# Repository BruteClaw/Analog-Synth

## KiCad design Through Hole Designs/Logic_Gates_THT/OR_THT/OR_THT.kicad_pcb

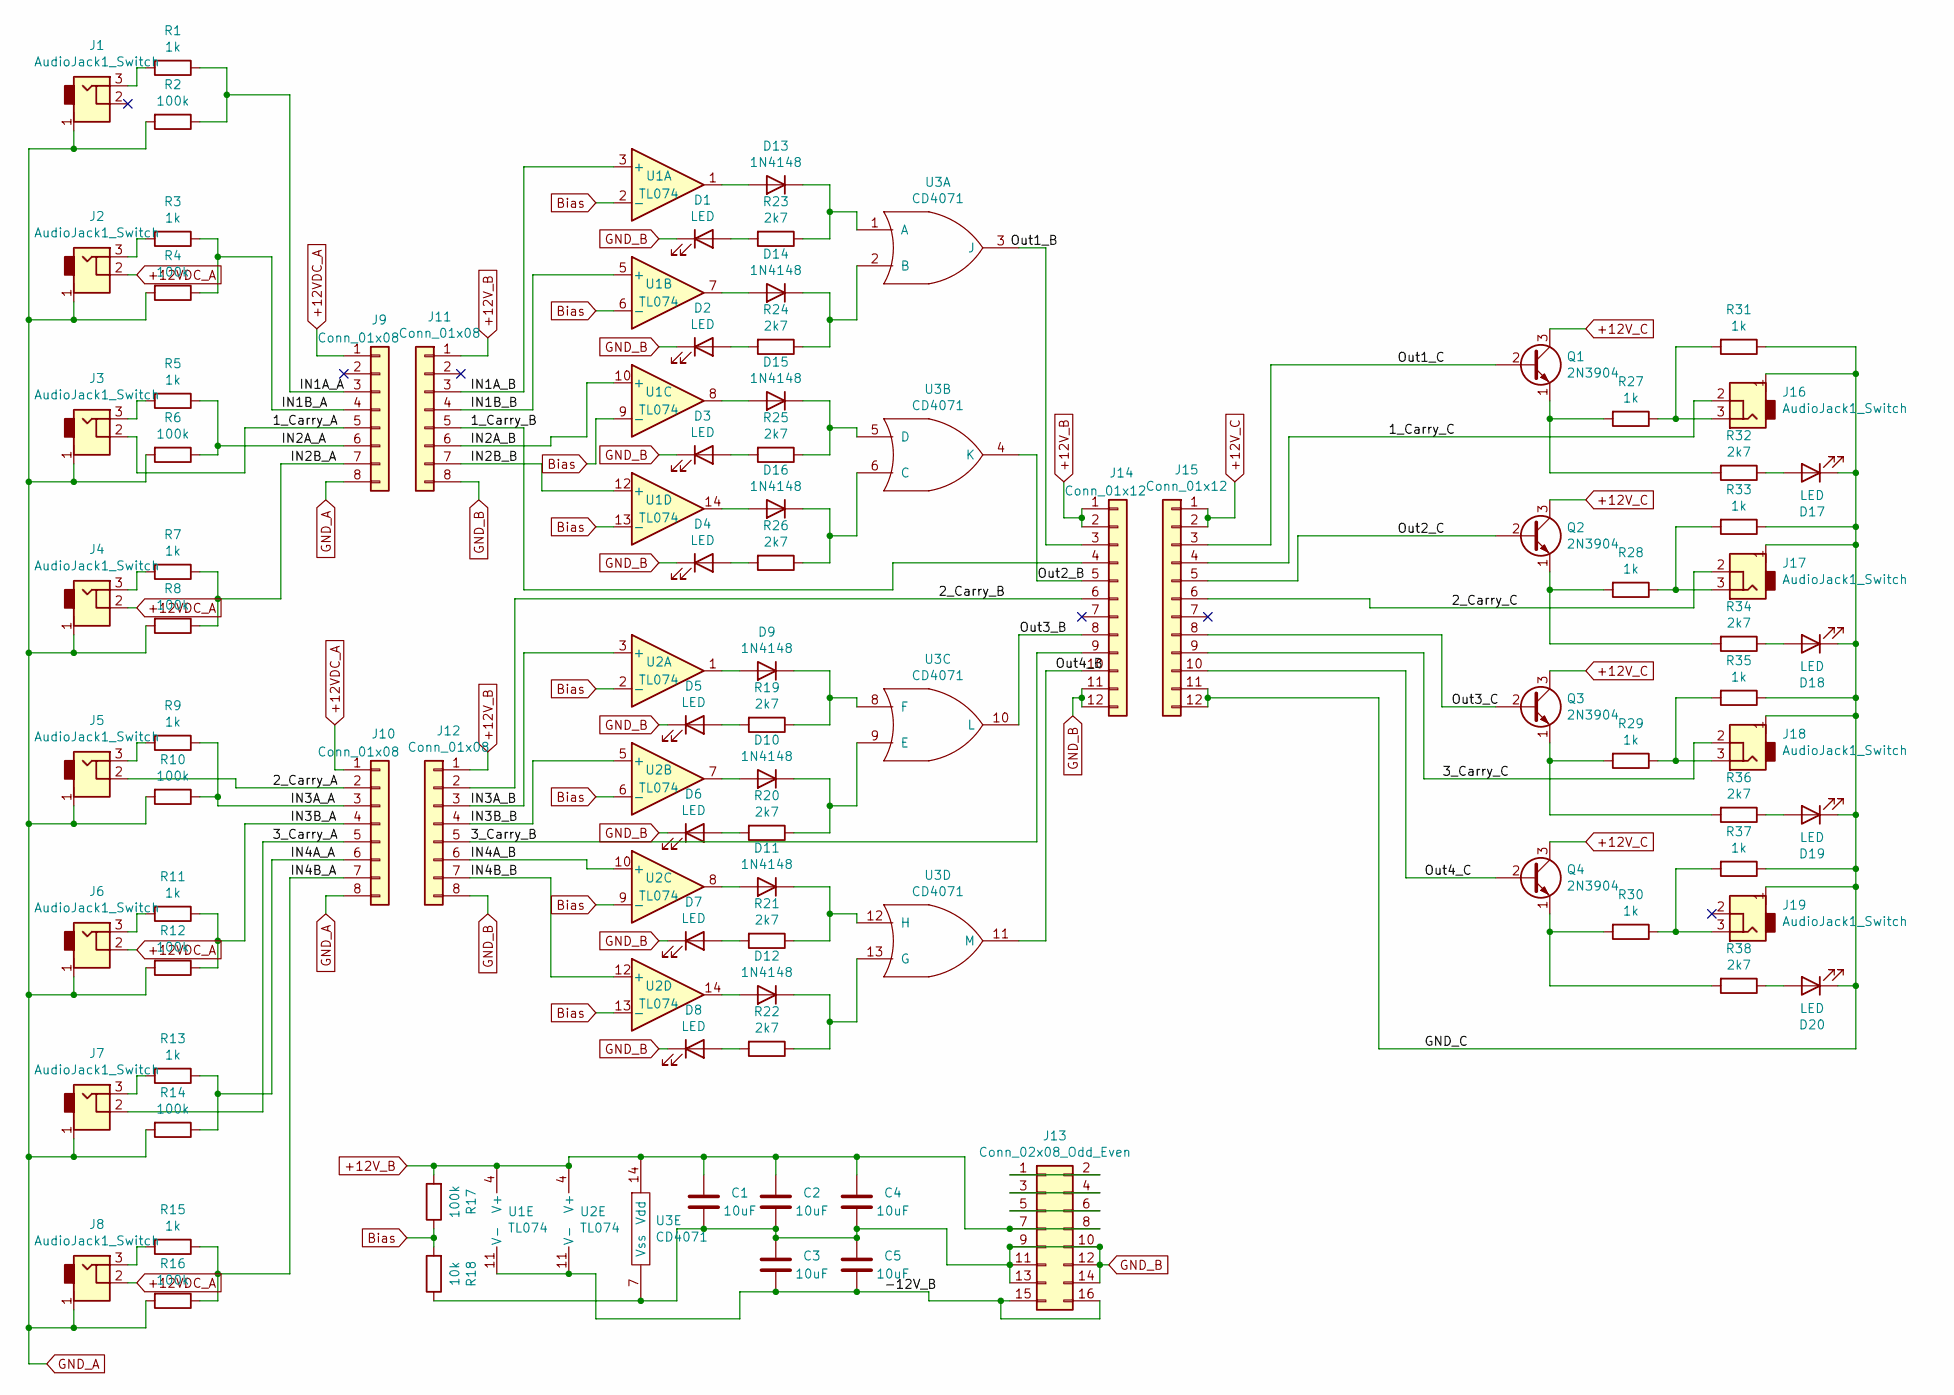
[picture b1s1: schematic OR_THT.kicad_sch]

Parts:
C1, C2, C3, C4, C5: 10uF; C_Disc_D5.0mm_W2.5mm_P2.50mm
D1, D2, D3, D4, D5, D6, D7, D8, D17, D18, D19, D20: LED; LED_Rectangular_W3.9mm_H1.9mm
D9, D10, D11, D12, D13, D14, D15, D16: 1N4148; D_DO-35_SOD27_P7.62mm_Horizontal
J1, J2, J3, J4, J5, J6, J7, J8, J16, J17, J18, J19: AudioJack1_Switch; Mono_Jack_3.5mm_Switch_Switchcraft_35RAPC2AH3
J9, J10, J11, J12: Conn_01x08; Pin_Header_Straight_1x08_Pitch2.54mm
J13: Conn_02x08_Odd_Even; Pin_Header_Straight_2x08_Pitch2.54mm
J14, J15: Conn_01x12; Pin_Header_Straight_1x12_Pitch2.54mm
Q1, Q2, Q3, Q4: 2N3904; TO-92_Inline_Wide
R1, R3, R5, R7, R9, R11, R13, R15, R27, R28, R29, R30, R31, R33, R35, R37: 1k; R_Axial_DIN0207_L6.3mm_D2.5mm_P10.16mm_Horizontal
R2, R4, R6, R8, R10, R12, R14, R16, R17: 100k; R_Axial_DIN0207_L6.3mm_D2.5mm_P10.16mm_Horizontal
R18: 10k; R_Axial_DIN0207_L6.3mm_D2.5mm_P10.16mm_Horizontal
R19, R20, R21, R22, R23, R24, R25, R26, R32, R34, R36, R38: 2k7; R_Axial_DIN0207_L6.3mm_D2.5mm_P10.16mm_Horizontal
U1, U2: TL074; DIP-14_W7.62mm_Socket
U3: CD4071; DIP-14_W7.62mm_Socket

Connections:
+12VDC_A: J2.2, J4.2, J6.2, J8.2, J9.1, J10.1
+12V_B: C1.2, C2.2, C4.2, J11.1, J12.1, J13.7, J13.8, J14.1, J14.2, R17.2, U1.4 (V+), U2.4 (V+), U3.14 (Vdd)
+12V_C: J15.1, J15.2, Q1.3 (C), Q2.3 (C), Q3.3 (C), Q4.3 (C)
/1_Carry_A: J3.2, J9.5
/1_Carry_B: J11.5, J14.4
/1_Carry_C: J15.4, J16.2
/2_Carry_A: J5.2, J10.2
/2_Carry_B: J12.2, J14.6
/2_Carry_C: J15.6, J17.2
/3_Carry_A: J7.2, J10.5
/3_Carry_B: J12.5, J14.9
/3_Carry_C: J15.9, J18.2
/-12V_B: C3.1, C5.1, J13.15, J13.16, U1.11 (V-), U2.11 (V-)
/GND_C: D17.1 (K), D18.1 (K), D19.1 (K), D20.1 (K), J15.11, J15.12, J16.1, J17.1, J18.1, J19.1, R31.1, R33.1, R35.1, R37.1
/IN1A_A: J9.3, R1.1, R2.1
/IN1A_B: J11.3, U1.3 (+)
/IN1B_A: J9.4, R3.1, R4.1
/IN1B_B: J11.4, U1.5 (+)
/IN2A_A: J9.6, R5.1, R6.1
/IN2A_B: J11.6, U1.10 (+)
/IN2B_A: J9.7, R7.1, R8.1
/IN2B_B: J11.7, U1.12 (+)
/IN3A_A: J10.3, R9.1, R10.1
/IN3A_B: J12.3, U2.3 (+)
/IN3B_A: J10.4, R11.1, R12.1
/IN3B_B: J12.4, U2.5 (+)
/IN4A_A: J10.6, R13.1, R14.1
/IN4A_B: J12.6, U2.10 (+)
/IN4B_A: J10.7, R15.1, R16.1
/IN4B_B: J12.7, U2.12 (+)
/Out1_C: J15.3, Q1.2 (B)
/Out2_B: J14.5, U3.4 (K)
/Out2_C: J15.5, Q2.2 (B)
/Out3_B: J14.8, U3.10 (L)
/Out3_C: J15.8, Q3.2 (B)
/Out4_B: J14.10, U3.11 (M)
/Out4_C: J15.10, Q4.2 (B)
Bias: R17.1, R18.2, U1.2 (-), U1.6 (-), U1.9 (-), U1.13 (-), U2.2 (-), U2.6 (-), U2.9 (-), U2.13 (-)
GND_A: J1.1, J2.1, J3.1, J4.1, J5.1, J6.1, J7.1, J8.1, J9.8, J10.8, R2.2, R4.2, R6.2, R8.2, R10.2, R12.2, R14.2, R16.2
GND_B: C1.1, C2.1, C3.2, C4.1, C5.2, D1.1 (K), D2.1 (K), D3.1 (K), D4.1 (K), D5.1 (K), D6.1 (K), D7.1 (K), D8.1 (K), J11.8, J12.8, J13.9, J13.10, J13.11, J13.12, J13.13, J13.14, J14.11, J14.12, R18.1, U3.7 (Vss)
unnamed: D1.2 (A), R23.2
unnamed: D2.2 (A), R24.2
unnamed: D3.2 (A), R25.2
unnamed: D4.2 (A), R26.2
unnamed: D5.2 (A), R19.2
unnamed: D6.2 (A), R20.2
unnamed: D7.2 (A), R21.2
unnamed: D8.2 (A), R22.2
unnamed: D9.1 (K), R19.1, U3.8 (F)
unnamed: D9.2 (A), U2.1
unnamed: D10.1 (K), R20.1, U3.9 (E)
unnamed: D10.2 (A), U2.7
unnamed: D11.1 (K), R21.1, U3.12 (H)
unnamed: D11.2 (A), U2.8
unnamed: D12.1 (K), R22.1, U3.13 (G)
unnamed: D12.2 (A), U2.14
unnamed: D13.1 (K), R23.1, U3.1 (A)
unnamed: D13.2 (A), U1.1
unnamed: D14.1 (K), R24.1, U3.2 (B)
unnamed: D14.2 (A), U1.7
unnamed: D15.1 (K), R25.1, U3.5 (D)
unnamed: D15.2 (A), U1.8
unnamed: D16.1 (K), R26.1, U3.6 (C)
unnamed: D16.2 (A), U1.14
unnamed: D17.2 (A), R32.1
unnamed: D18.2 (A), R34.1
unnamed: D19.2 (A), R36.1
unnamed: D20.2 (A), R38.1
unnamed: J1.3, R1.2
unnamed: J2.3, R3.2
unnamed: J3.3, R5.2
unnamed: J4.3, R7.2
unnamed: J5.3, R9.2
unnamed: J6.3, R11.2
unnamed: J7.3, R13.2
unnamed: J8.3, R15.2
unnamed: J13.1, J13.2
unnamed: J13.3, J13.4
unnamed: J13.5, J13.6
unnamed: J14.3, U3.3 (J)
unnamed: J16.3, R27.1, R31.2
unnamed: J17.3, R28.1, R33.2
unnamed: J18.3, R29.1, R35.2
unnamed: J19.3, R30.1, R37.2
unnamed: Q1.1 (E), R27.2, R32.2
unnamed: Q2.1 (E), R28.2, R34.2
unnamed: Q3.1 (E), R29.2, R36.2
unnamed: Q4.1 (E), R30.2, R38.2

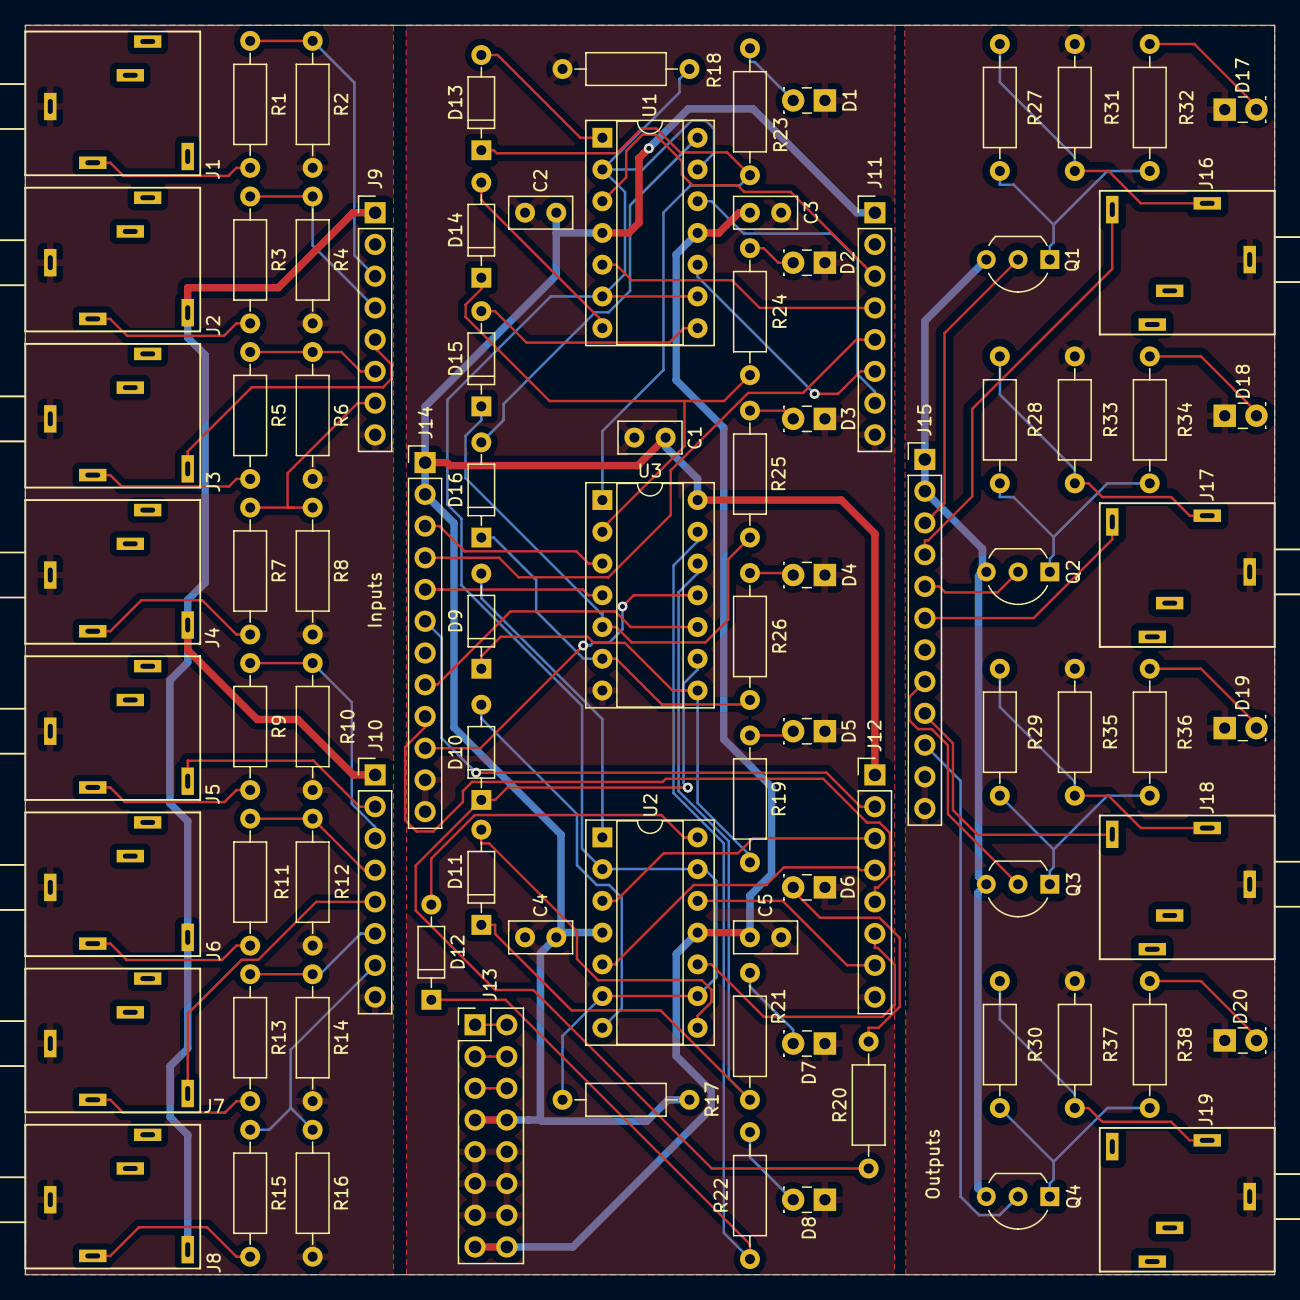
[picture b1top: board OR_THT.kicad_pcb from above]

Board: 2 copper layers, 100.0 x 100.0 mm, 89 parts (0 on the bottom side), 88 nets.

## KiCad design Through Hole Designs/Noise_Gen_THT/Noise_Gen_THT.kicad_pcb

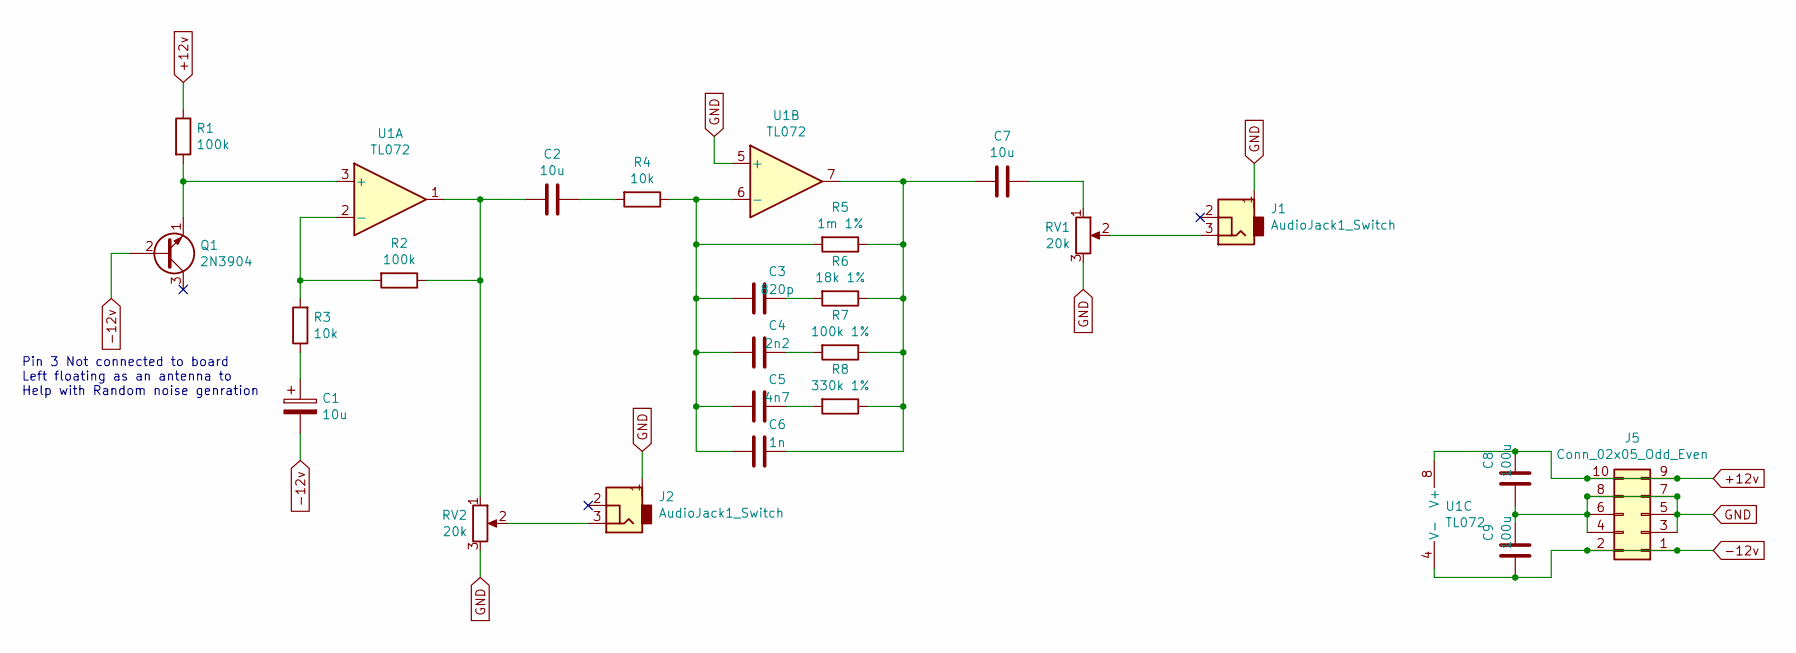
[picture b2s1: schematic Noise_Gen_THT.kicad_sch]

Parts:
C1: 10u; CP_Radial_D4.0mm_P1.50mm
C2, C7: 10u; C_Disc_D6.0mm_W4.4mm_P5.00mm
C3: 820p; C_Disc_D6.0mm_W4.4mm_P5.00mm
C4: 2n2; C_Disc_D6.0mm_W4.4mm_P5.00mm
C5: 4n7; C_Disc_D6.0mm_W4.4mm_P5.00mm
C6: 1n; C_Disc_D6.0mm_W4.4mm_P5.00mm
C8, C9: 100u; CP_Radial_D5.0mm_P2.00mm
J1, J2: AudioJack1_Switch; Mono_Jack_3.5mm_Switch_Switchcraft_35RAPC2AH3
J5: Conn_02x05_Odd_Even; Pin_Header_Straight_2x05_Pitch2.54mm
Q1: 2N3904; TO-92_Inline_Wide
R1, R2: 100k; R_Axial_DIN0207_L6.3mm_D2.5mm_P10.16mm_Horizontal
R3, R4: 10k; R_Axial_DIN0207_L6.3mm_D2.5mm_P10.16mm_Horizontal
R5: 1m 1%; R_Axial_DIN0207_L6.3mm_D2.5mm_P10.16mm_Horizontal
R6: 18k 1%; R_Axial_DIN0207_L6.3mm_D2.5mm_P10.16mm_Horizontal
R7: 100k 1%; R_Axial_DIN0207_L6.3mm_D2.5mm_P10.16mm_Horizontal
R8: 330k 1%; R_Axial_DIN0207_L6.3mm_D2.5mm_P10.16mm_Horizontal
RV1, RV2: 20k; Potentiometer_Bourns_PTV09A-2_Vertical
U1: TL072; DIP-8_W7.62mm_Socket

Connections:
+12v: C8.1, J5.9, J5.10, R1.1, U1.8 (V+)
-12v: C1.2, C9.2, J5.1, J5.2, Q1.2 (B), U1.4 (V-)
GND: C8.2, C9.1, J1.1, J2.1, J5.3, J5.4, J5.5, J5.6, J5.7, J5.8, RV1.3, RV2.3, U1.5 (+)
unnamed: C1.1, R3.1
unnamed: C2.1, R4.2
unnamed: C2.2, R2.1, RV2.1, U1.1
unnamed: C3.1, R6.2
unnamed: C3.2, C4.2, C5.2, C6.2, R4.1, R5.2, U1.6 (-)
unnamed: C4.1, R7.2
unnamed: C5.1, R8.2
unnamed: C6.1, C7.2, R5.1, R6.1, R7.1, R8.1, U1.7
unnamed: C7.1, RV1.1
unnamed: J1.3, RV1.2
unnamed: J2.3, RV2.2
unnamed: Q1.1 (E), R1.2, U1.3 (+)
unnamed: R2.2, R3.2, U1.2 (-)

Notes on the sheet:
Pin 3 Not connected to board Left floating as an antenna to Help with Random noise genration

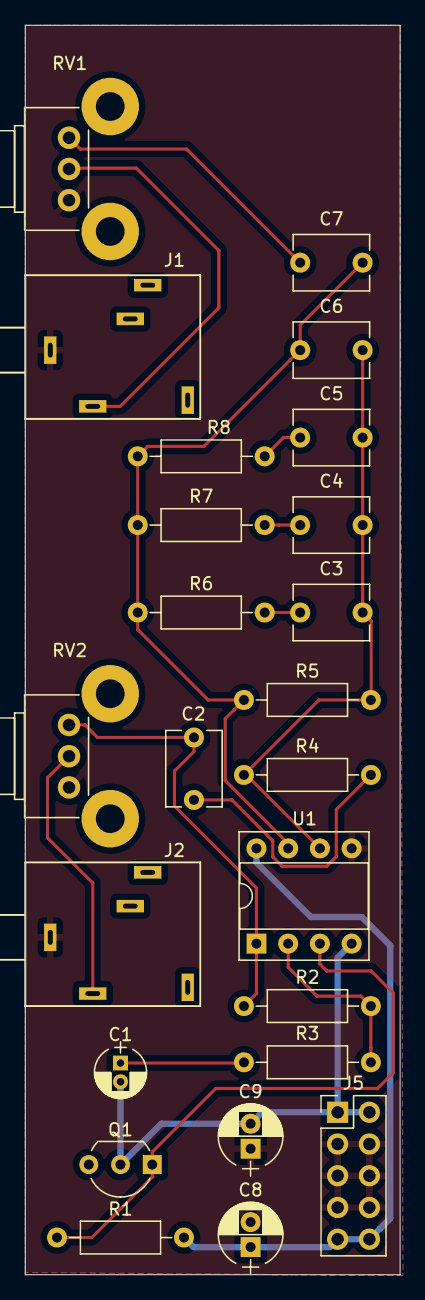
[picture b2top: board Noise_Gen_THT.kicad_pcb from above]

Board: 2 copper layers, 30.0 x 100.0 mm, 24 parts (0 on the bottom side), 16 nets.

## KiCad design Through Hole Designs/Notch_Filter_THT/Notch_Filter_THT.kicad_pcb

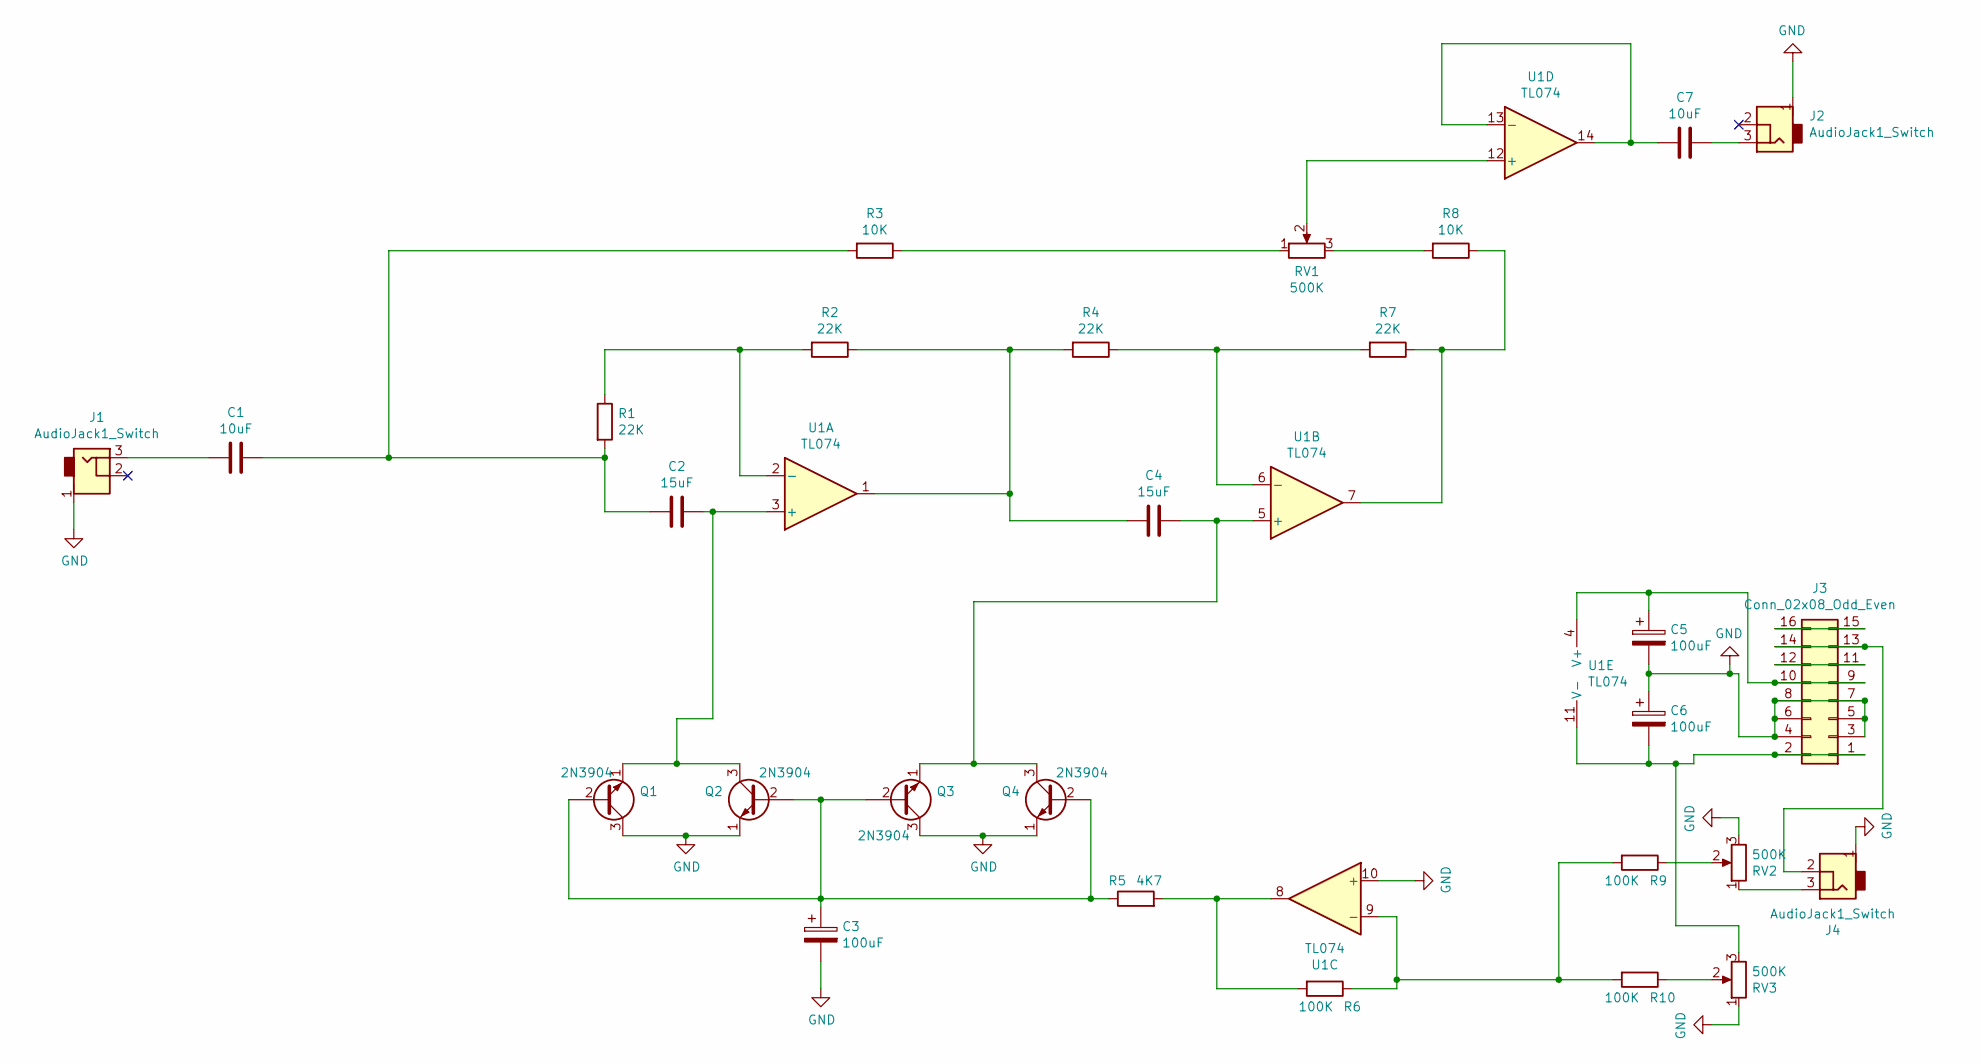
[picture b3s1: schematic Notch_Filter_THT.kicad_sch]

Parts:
C1, C7: 10uF; C_Disc_D5.0mm_W2.5mm_P2.50mm
C2, C4: 15uF; C_Disc_D5.0mm_W2.5mm_P2.50mm
C3, C5, C6: 100uF; CP_Radial_D6.3mm_P2.50mm
J1, J2, J4: AudioJack1_Switch; Mono_Jack_3.5mm_Switch_Switchcraft_35RAPC2AH3
J3: Conn_02x08_Odd_Even; Pin_Header_Straight_2x08_Pitch2.54mm
Q1, Q2, Q3, Q4: 2N3904; TO-92_Inline_Wide
R1, R2, R4, R7: 22K; R_Axial_DIN0207_L6.3mm_D2.5mm_P10.16mm_Horizontal
R3, R8: 10K; R_Axial_DIN0207_L6.3mm_D2.5mm_P10.16mm_Horizontal
R5: 4K7; R_Axial_DIN0207_L6.3mm_D2.5mm_P10.16mm_Horizontal
R6, R9, R10: 100K; R_Axial_DIN0207_L6.3mm_D2.5mm_P10.16mm_Horizontal
RV1, RV2, RV3: 500K; Potentiometer_Bourns_PTV09A-2_Vertical
U1: TL074; DIP-14_W7.62mm_Socket

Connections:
GND: C3.2, C5.2, C6.1, J1.1, J2.1, J3.3, J3.4, J3.5, J3.6, J3.7, J3.8, J4.1, Q1.3 (C), Q2.1 (E), Q3.3 (C), Q4.1 (E), RV2.3, RV3.1, U1.10 (+)
unnamed: C1.1, C2.2, R1.2, R3.2
unnamed: C1.2, J1.3
unnamed: C2.1, Q1.1 (E), Q2.3 (C), U1.3 (+)
unnamed: C3.1, Q1.2 (B), Q2.2 (B), Q3.2 (B), Q4.2 (B), R5.1
unnamed: C4.1, Q3.1 (E), Q4.3 (C), U1.5 (+)
unnamed: C4.2, R2.1, R4.2, U1.1
unnamed: C5.1, J3.9, J3.10, U1.4 (V+)
unnamed: C6.2, J3.1, J3.2, RV3.3, U1.11 (V-)
unnamed: C7.1, J2.3
unnamed: C7.2, U1.13 (-), U1.14
unnamed: J3.11, J3.12
unnamed: J3.13, J3.14, J4.2
unnamed: J3.15, J3.16
unnamed: J4.3, RV2.1
unnamed: R1.1, R2.2, U1.2 (-)
unnamed: R3.1, RV1.1
unnamed: R4.1, R7.2, U1.6 (-)
unnamed: R5.2, R6.2, U1.8
unnamed: R7.1, R8.1, U1.7
unnamed: R8.2, RV1.3
unnamed: R9.1, RV2.2
unnamed: R10.1, RV3.2
unnamed: R6.1, R9.2, R10.2, U1.9 (-)
unnamed: RV1.2, U1.12 (+)

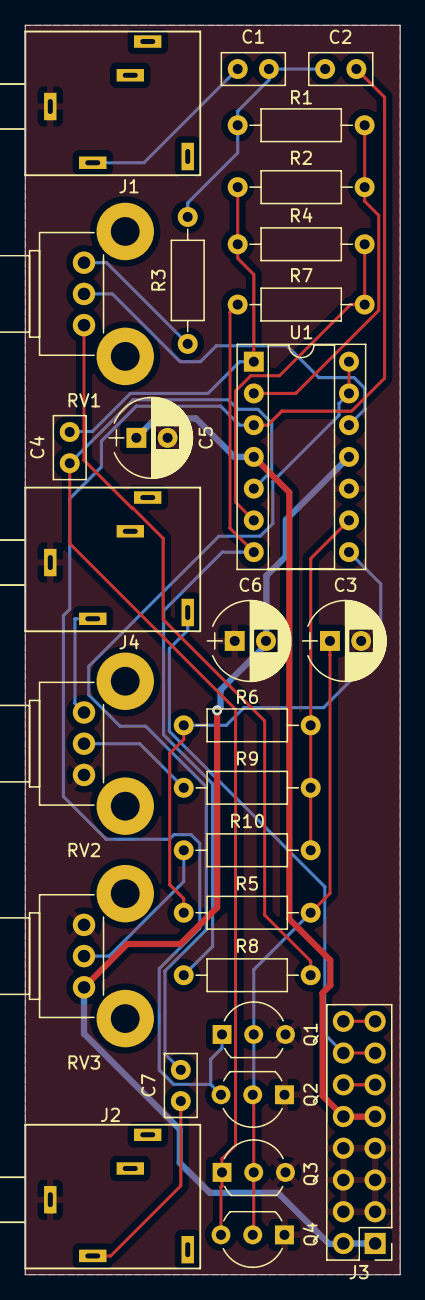
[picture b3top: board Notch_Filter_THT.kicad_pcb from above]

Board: 2 copper layers, 30.0 x 100.0 mm, 29 parts (0 on the bottom side), 25 nets.

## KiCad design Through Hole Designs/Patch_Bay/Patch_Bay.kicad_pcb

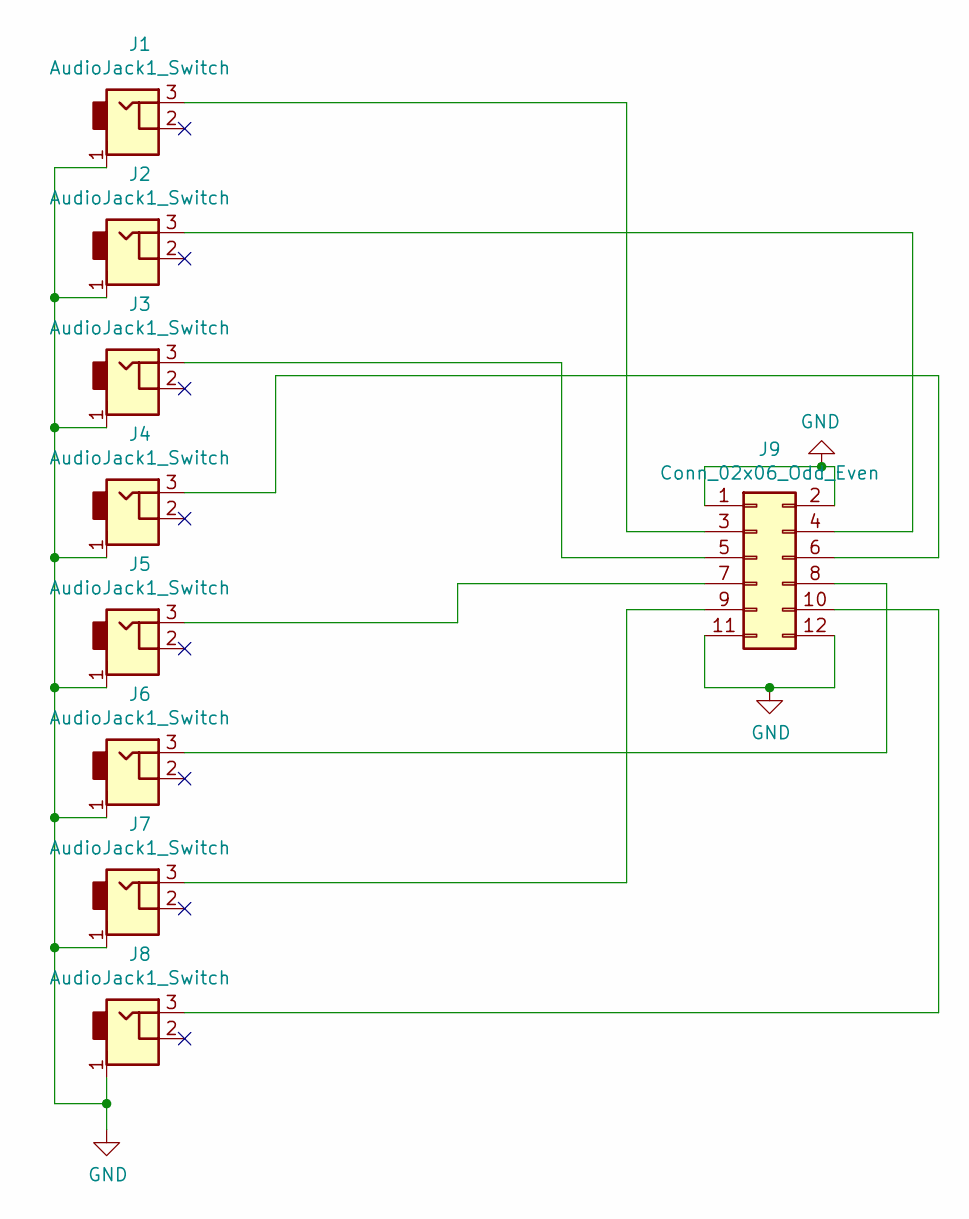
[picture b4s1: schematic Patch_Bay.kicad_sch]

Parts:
J1, J2, J3, J4, J5, J6, J7, J8: AudioJack1_Switch; Mono_Jack_3.5mm_Switch_Switchcraft_35RAPC2AH3
J9: Conn_02x06_Odd_Even; Pin_Header_Straight_2x06_Pitch2.54mm

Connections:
GND: J1.1, J2.1, J3.1, J4.1, J5.1, J6.1, J7.1, J8.1, J9.1, J9.2, J9.11, J9.12
unnamed: J1.3, J9.3
unnamed: J2.3, J9.4
unnamed: J3.3, J9.5
unnamed: J4.3, J9.6
unnamed: J5.3, J9.7
unnamed: J6.3, J9.8
unnamed: J7.3, J9.9
unnamed: J8.3, J9.10

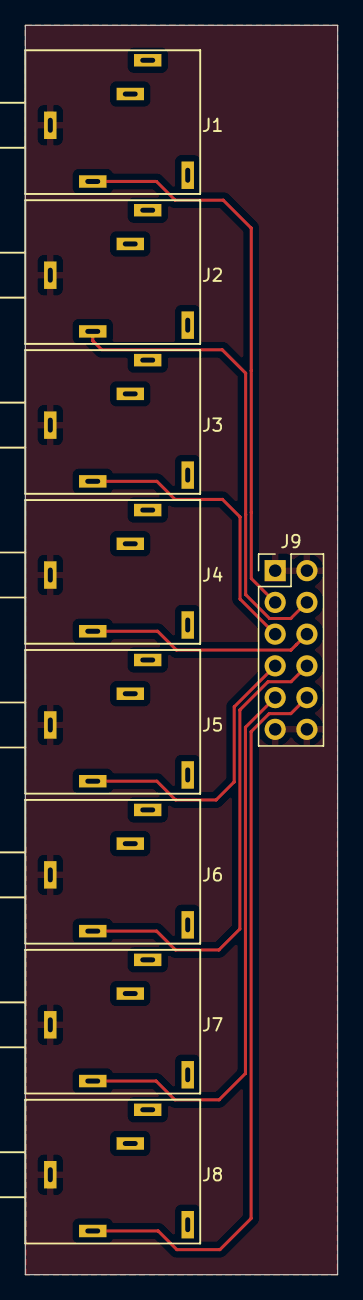
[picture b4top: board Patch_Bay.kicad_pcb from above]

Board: 2 copper layers, 25.0 x 100.0 mm, 9 parts (0 on the bottom side), 9 nets.

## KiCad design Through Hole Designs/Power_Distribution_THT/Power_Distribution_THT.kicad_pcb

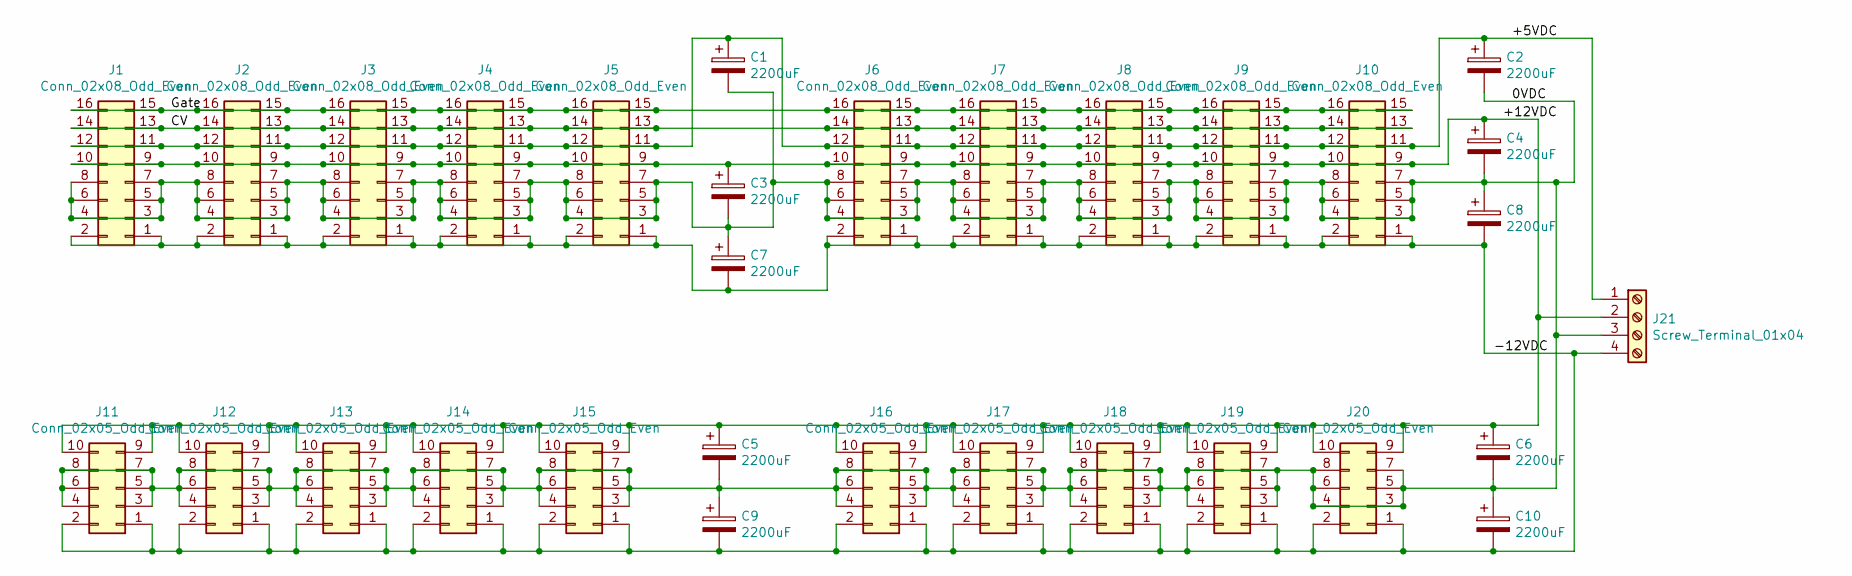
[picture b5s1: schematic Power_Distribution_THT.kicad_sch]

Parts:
C1, C2, C3, C4, C5, C6, C7, C8, C9, C10: 2200uF; CP_Radial_D16.0mm_P7.50mm
J1, J2, J3, J4, J5, J6, J7, J8, J9, J10: Conn_02x08_Odd_Even; Socket_Strip_Straight_2x08_Pitch2.54mm
J11, J12, J13, J14, J15, J16, J17, J18, J19, J20: Conn_02x05_Odd_Even; Socket_Strip_Straight_2x05_Pitch2.54mm
J21: Screw_Terminal_01x04; TerminalBlock_bornier-4_P5.08mm

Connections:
/0VDC: C1.2, C2.2, C3.2, C4.2, C5.2, C6.2, C7.1, C8.1, C9.1, C10.1, J1.3, J1.4, J1.5, J1.6, J1.7, J1.8, J2.3, J2.4, J2.5, J2.6, J2.7, J2.8, J3.3, J3.4, J3.5, J3.6, J3.7, J3.8, J4.3, J4.4, J4.5, J4.6, J4.7, J4.8, J5.3, J5.4, J5.5, J5.6, J5.7, J5.8, J6.3, J6.4, J6.5, J6.6, J6.7, J6.8, J7.3, J7.4, J7.5, J7.6, J7.7, J7.8, J8.3, J8.4, J8.5, J8.6, J8.7, J8.8, J9.3, J9.4, J9.5, J9.6, J9.7, J9.8, J10.3, J10.4, J10.5, J10.6, J10.7, J10.8, J11.3, J11.4, J11.5, J11.6, J11.7, J11.8, J12.3, J12.4, J12.5, J12.6, J12.7, J12.8, J13.3, J13.4, J13.5, J13.6, J13.7, J13.8, J14.3, J14.4, J14.5, J14.6, J14.7, J14.8, J15.3, J15.4, J15.5, J15.6, J15.7, J15.8, J16.3, J16.4, J16.5, J16.6, J16.7, J16.8, J17.3, J17.4, J17.5, J17.6, J17.7, J17.8, J18.3, J18.4, J18.5, J18.6, J18.7, J18.8, J19.3, J19.4, J19.5, J19.6, J19.7, J19.8, J20.3, J20.4, J20.5, J20.6, J20.7, J20.8, J21.3
/+5VDC: C1.1, C2.1, J1.11, J1.12, J2.11, J2.12, J3.11, J3.12, J4.11, J4.12, J5.11, J5.12, J6.11, J6.12, J7.11, J7.12, J8.11, J8.12, J9.11, J9.12, J10.11, J10.12, J21.1
/+12VDC: C3.1, C4.1, C5.1, C6.1, J1.9, J1.10, J2.9, J2.10, J3.9, J3.10, J4.9, J4.10, J5.9, J5.10, J6.9, J6.10, J7.9, J7.10, J8.9, J8.10, J9.9, J9.10, J10.9, J10.10, J11.9, J11.10, J12.9, J12.10, J13.9, J13.10, J14.9, J14.10, J15.9, J15.10, J16.9, J16.10, J17.9, J17.10, J18.9, J18.10, J19.9, J19.10, J20.9, J20.10, J21.2
/-12VDC: C7.2, C8.2, C9.2, C10.2, J1.1, J1.2, J2.1, J2.2, J3.1, J3.2, J4.1, J4.2, J5.1, J5.2, J6.1, J6.2, J7.1, J7.2, J8.1, J8.2, J9.1, J9.2, J10.1, J10.2, J11.1, J11.2, J12.1, J12.2, J13.1, J13.2, J14.1, J14.2, J15.1, J15.2, J16.1, J16.2, J17.1, J17.2, J18.1, J18.2, J19.1, J19.2, J20.1, J20.2, J21.4
/CV: J1.13, J1.14, J2.13, J2.14, J3.13, J3.14, J4.13, J4.14, J5.13, J5.14, J6.13, J6.14, J7.13, J7.14, J8.13, J8.14, J9.13, J9.14, J10.13, J10.14
/Gate: J1.15, J1.16, J2.15, J2.16, J3.15, J3.16, J4.15, J4.16, J5.15, J5.16, J6.15, J6.16, J7.15, J7.16, J8.15, J8.16, J9.15, J9.16, J10.15, J10.16

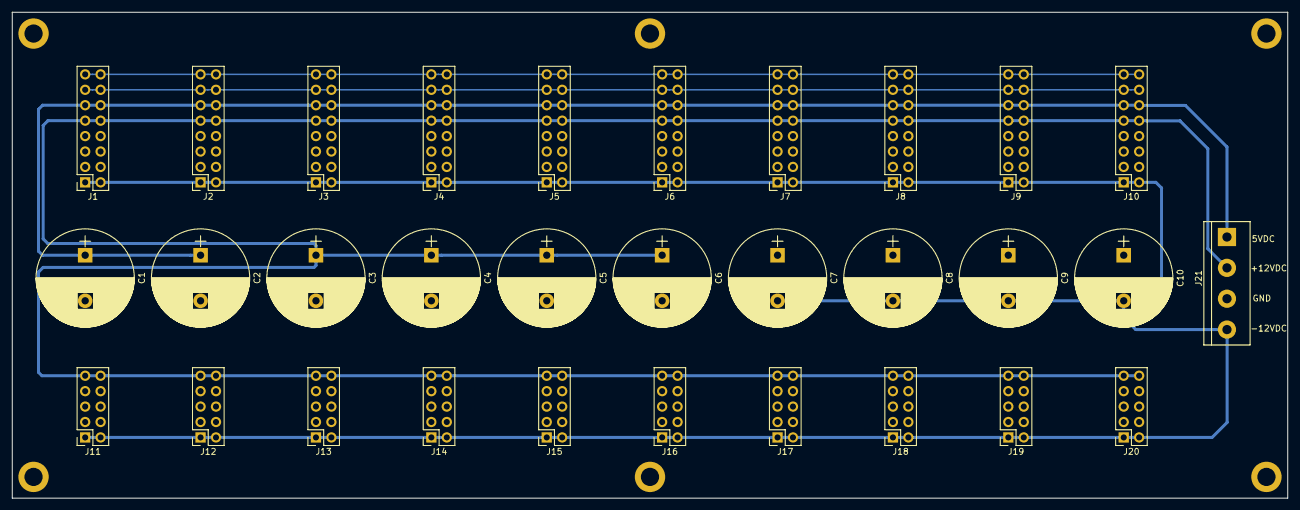
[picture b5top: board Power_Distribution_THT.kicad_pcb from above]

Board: 2 copper layers, 210.0 x 80.0 mm, 31 parts (0 on the bottom side), 6 nets.

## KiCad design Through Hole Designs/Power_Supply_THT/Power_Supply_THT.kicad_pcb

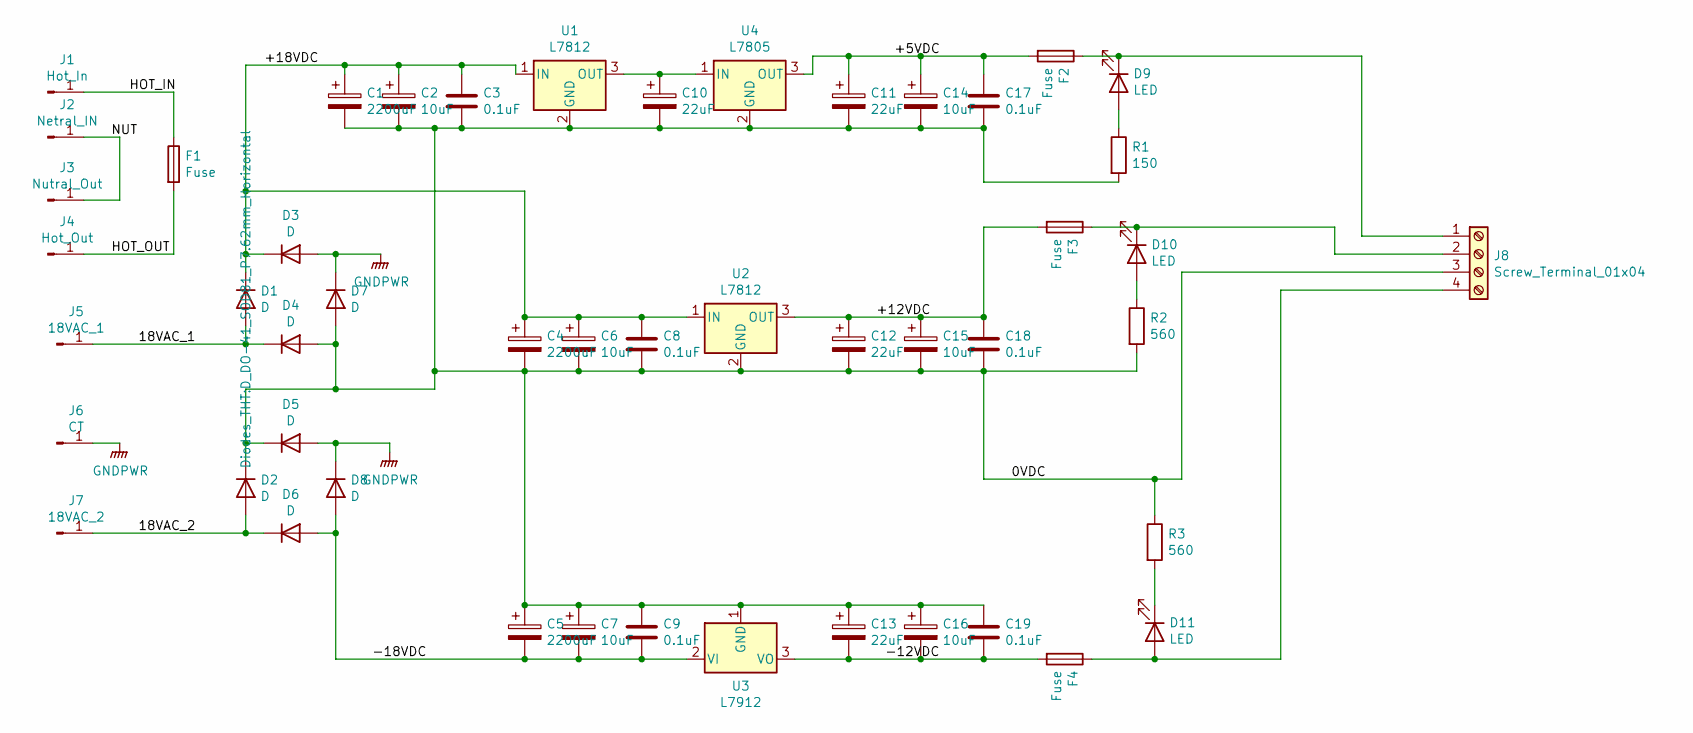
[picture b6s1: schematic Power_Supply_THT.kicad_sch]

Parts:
C1, C4, C5: 2200uF; CP_Radial_D16.0mm_P7.50mm
C2, C6, C7, C14, C15, C16: 10uF; CP_Radial_D5.0mm_P2.00mm
C3, C8, C9, C17, C18, C19: 0.1uF; C_Disc_D4.7mm_W2.5mm_P5.00mm
C10, C11, C12, C13: 22uF; CP_Radial_D5.0mm_P2.00mm
D1, D2, D3, D4, D5, D6, D7, D8: D; D_DO-41_SOD81_P7.62mm_Horizontal
D9, D10, D11: LED; LED_D5.0mm
F1, F2, F3, F4: Fuse; Fuseholder5x20_horiz_open_inline_Type-I
J1: Hot_In; TAB_Conn
J2: Netral_IN; TAB_Conn
J3: Nutral_Out; TAB_Conn
J4: Hot_Out; TAB_Conn
J5: 18VAC_1; TAB_Conn
J6: CT; TAB_Conn
J7: 18VAC_2; TAB_Conn
J8: Screw_Terminal_01x04; TerminalBlock_bornier-4_P5.08mm
R1: 150; R_Axial_DIN0207_L6.3mm_D2.5mm_P7.62mm_Horizontal
R2, R3: 560; R_Axial_DIN0207_L6.3mm_D2.5mm_P7.62mm_Horizontal
U1, U2: L7812; TO-220-3_Vertical
U3: L7912; TO-220-3_Vertical
U4: L7805; TO-220-3_Vertical

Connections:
/0VDC: C1.2, C2.2, C3.2, C4.2, C5.1, C6.2, C7.1, C8.2, C9.1, C10.2, C11.2, C12.2, C13.1, C14.2, C15.2, C16.1, C17.2, C18.2, C19.1, D2.1 (K), D4.2 (A), D5.1 (K), D7.2 (A), J8.3, R1.2, R2.2, R3.1, U1.2 (GND), U2.2 (GND), U3.1 (GND), U4.2 (GND)
/18VAC_1: D1.2 (A), D4.1 (K), J5.1
/18VAC_2: D2.2 (A), D6.1 (K), J7.1
/+5VDC: C11.1, C14.1, C17.1, F2.2, U4.3 (OUT)
/+12VDC: C12.1, C15.1, C18.1, F3.2, U2.3 (OUT)
/+18VDC: C1.1, C2.1, C3.1, C4.1, C6.1, C8.1, D1.1 (K), D3.1 (K), U1.1 (IN), U2.1 (IN)
/-12VDC: C13.2, C16.2, C19.2, F4.2, U3.3 (VO)
/-18VDC: C5.2, C7.2, C9.2, D6.2 (A), D8.2 (A), U3.2 (VI)
/HOT_IN: F1.1, J1.1
/HOT_OUT: F1.2, J4.1
/NUT: J2.1, J3.1
GNDPWR: D3.2 (A), D5.2 (A), D7.1 (K), D8.1 (K), J6.1
unnamed: C10.1, U1.3 (OUT), U4.1 (IN)
unnamed: D9.1 (K), F2.1, J8.1
unnamed: D9.2 (A), R1.1
unnamed: D10.1 (K), F3.1, J8.2
unnamed: D10.2 (A), R2.1
unnamed: D11.1 (K), R3.2
unnamed: D11.2 (A), F4.1, J8.4

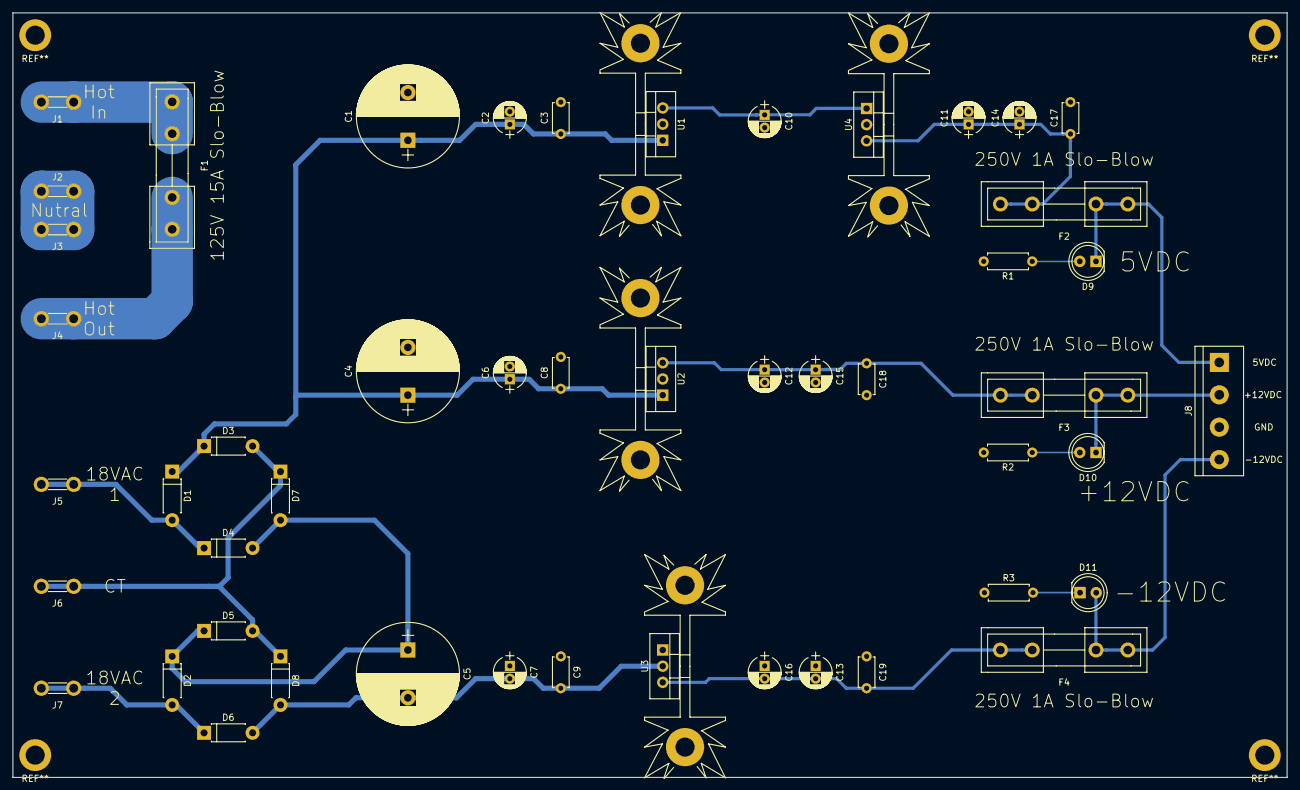
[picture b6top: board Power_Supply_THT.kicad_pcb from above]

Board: 2 copper layers, 200.0 x 120.0 mm, 49 parts (0 on the bottom side), 19 nets.
